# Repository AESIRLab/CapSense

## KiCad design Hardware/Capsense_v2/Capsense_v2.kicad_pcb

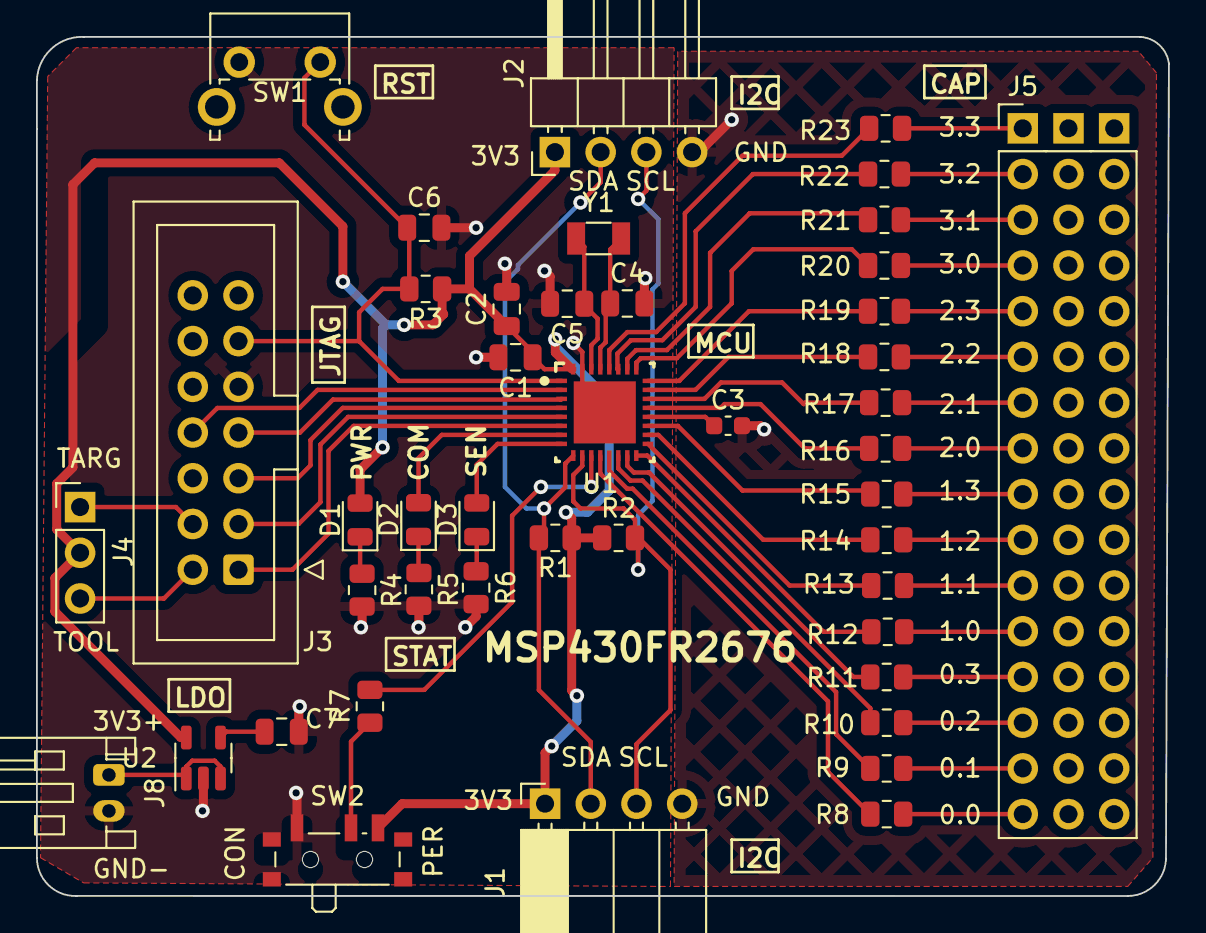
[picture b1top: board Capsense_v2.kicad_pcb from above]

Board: 2 copper layers, 62.9 x 47.7 mm, 44 parts (0 on the bottom side), 56 nets.

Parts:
C1: 4u7; C_0805_2012Metric
C2: 10u; C_0805_2012Metric
C3: 0u1; C_0603_1608Metric
C4, C5: 22p; C_0805_2012Metric
C6: 1n; C_0805_2012Metric
C7: 10n; C_0805_2012Metric
D1: GREEN; LED_0805_2012Metric
D2: RED; LED_0805_2012Metric
D3: BLUE; LED_0805_2012Metric
J1: Conn_01x04; PinSocket_1x04_P2.54mm_Horizontal
J2: Conn_01x04; PinHeader_1x04_P2.54mm_Horizontal
J3: Conn_02x07_Odd_Even; IDC-Header_2x07_P2.54mm_Vertical
J4: Conn_01x03; PinHeader_1x03_P2.54mm_Vertical
J5: DINA; CSA_48PN_RECPT
J8: Conn_01x02; JST_PH_S2B-PH-K_1x02_P2.00mm_Horizontal
R1, R2, R4, R5, R6, R7: 10k; R_0805_2012Metric
R3: 47k; R_0805_2012Metric
R8, R9, R10, R11, R12, R13, R14, R15, R16, R17, R18, R19, R20, R21, R22, R23: 470; R_0805_2012Metric
SW1: SW_Push; SW_Tactile_SPST_Angled_PTS645Vx39-2LFS
SW2: SW_SPDT; SW_SPDT_PCM12
U1: MSP430FR2676TRHBR; RHB0032E
U2: TPS73633DBV; SOT-23-5
Y1: 32k768; Crystal_SMD_3215-2Pin_3.2x1.5mm

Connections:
+3V3: C1.1, C2.1, D1.2 (A), J1.1, J2.1, J4.2, R1.1, R2.1, R3.1, SW2.3 (C), U1.32 (DVCC), U2.5 (OUT)
/I2C_SCL: J1.3, J2.3, R2.2, U1.10 (P1.3_UCB0SOMI_UCB0SCL_MCLK_A3)
/I2C_SDA: J1.2, J2.2, R1.2, U1.9 (P1.2_UCB0SIMO_UCB0SDA_TA0.2_A2_VEREF-)
/P1.0_LED: D2.2 (A), U1.7 (P1.0_UCB0STE_TA0CLK_A0_VEREF+)
/P1.1_LED: D3.2 (A), U1.8 (P1.1_UCB0CLK_TA0.1_COMP0.0_A1)
/P2.2_MODE: R7.2, U1.11 (P2.2_SYNC_ACLK_COMP0.1)
/RST: C6.1, J3.11, R3.2, SW1.2, U1.1 (RST_NMI_SBWTDIO_N)
/TCK: J3.7, U1.3 (P1.4_UCA0TXD_UCA0SIMO_TA1.2_TCK_A4_VREF+)
/TDI: J3.3, U1.5 (P1.6_UCA0CLK_TA1CLK_TDI_TCLK_A6)
/TDO: J3.1, U1.6 (P1.7_UCA0STE_SMCLK_TDO_A7)
/TEST: J3.8, U1.2 (TEST_SBWTCK)
/TMS: J3.5, U1.4 (P1.5_UCA0RXD_UCA0SOMI_TA1.1_TMS_A5)
/VCC_TARGET: J3.4, J4.1
/VCC_TOOL: J3.2, J4.3
/VREG: C3.1, U1.20 (VREG)
/XIN: C5.1, U1.30 (P2.1_XIN), Y1.2
/XOUT: C4.1, U1.29 (P2.0_XOUT), Y1.1
CAP0.0: R8.1, U1.12 (P3.0_TA2.2_CAP0.0)
CAP0.1: R9.1, U1.13 (P3.3_TA2.1_CAP0.1)
CAP0.2: R10.1, U1.14 (P2.3_TA2.0_CAP0.2)
CAP0.3: R11.1, U1.15 (P3.4_TA2CLK_COMP0OUT_CAP0.3)
CAP1.0: R12.1, U1.16 (P3.1_UCA1STE_CAP1.0)
CAP1.1: R13.1, U1.17 (P2.4_UCA1CLK_CAP1.1)
CAP1.2: R14.1, U1.18 (P2.5_UCA1RXD_UCA1SOMI_CAP1.2)
CAP1.3: R15.1, U1.19 (P2.6_UCA1TXD_UCA1SIMO_CAP1.3)
CAP2.0: R16.1, U1.21 (P3.7_TA3.2_CAP2.0)
CAP2.1: R17.1, U1.22 (P4.0_TA3.1_CAP2.1)
CAP2.2: R18.1, U1.23 (P4.1_TA3.0_CAP2.2)
CAP2.3: R19.1, U1.24 (P4.2_TA3CLK_CAP2.3)
CAP3.0: R20.1, U1.25 (P2.7_UCB1STE_CAP3.0)
CAP3.1: R21.1, U1.26 (P3.5_UCB1CLK_TB0TRG_CAP3.1)
CAP3.2: R22.1, U1.27 (P3.2_UCB1SIMO_UCB1SDA_CAP3.2)
CAP3.3: R23.1, U1.28 (P3.6_UCB1SOMI_UCB1SCL_CAP3.3)
GND: C1.2, C2.2, C3.2, C4.2, C5.2, C6.2, C7.2, J1.4, J2.4, J3.9, J8.2, R4.2, R5.2, R6.2, SW1.1, SW2.1 (A), U1.31 (DVSS), U1.33 (PAD), U2.2 (GND)
unnamed: D1.1 (K), R4.1
unnamed: D2.1 (K), R5.1
unnamed: D3.1 (K), R6.1
unnamed: J5.1, R23.2
unnamed: J5.2, R22.2
unnamed: J5.3, R21.2
unnamed: J5.4, R20.2
unnamed: J5.5, R19.2
unnamed: J5.6, R18.2
unnamed: J5.7, R17.2
unnamed: J5.8, R16.2
unnamed: J5.9, R15.2
unnamed: J5.10, R14.2
unnamed: J5.11, R13.2
unnamed: J5.12, R12.2
unnamed: J5.13, R11.2
unnamed: J5.14, R10.2
unnamed: J5.15, R9.2
unnamed: J5.16, R8.2
unnamed: J8.1, U2.1 (IN), U2.3 (EN)
unnamed: R7.1, SW2.2 (B)
unnamed: C7.1, U2.4 (NR)

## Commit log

2024-01-04 Added I2C and JTAG in Schematic
2024-01-04 Added Unfinished Arduino Support
2024-01-05 Completed Schematic for Version 2
2024-01-06 Completed PCB Layout
2024-01-06 Created HW Documentation
